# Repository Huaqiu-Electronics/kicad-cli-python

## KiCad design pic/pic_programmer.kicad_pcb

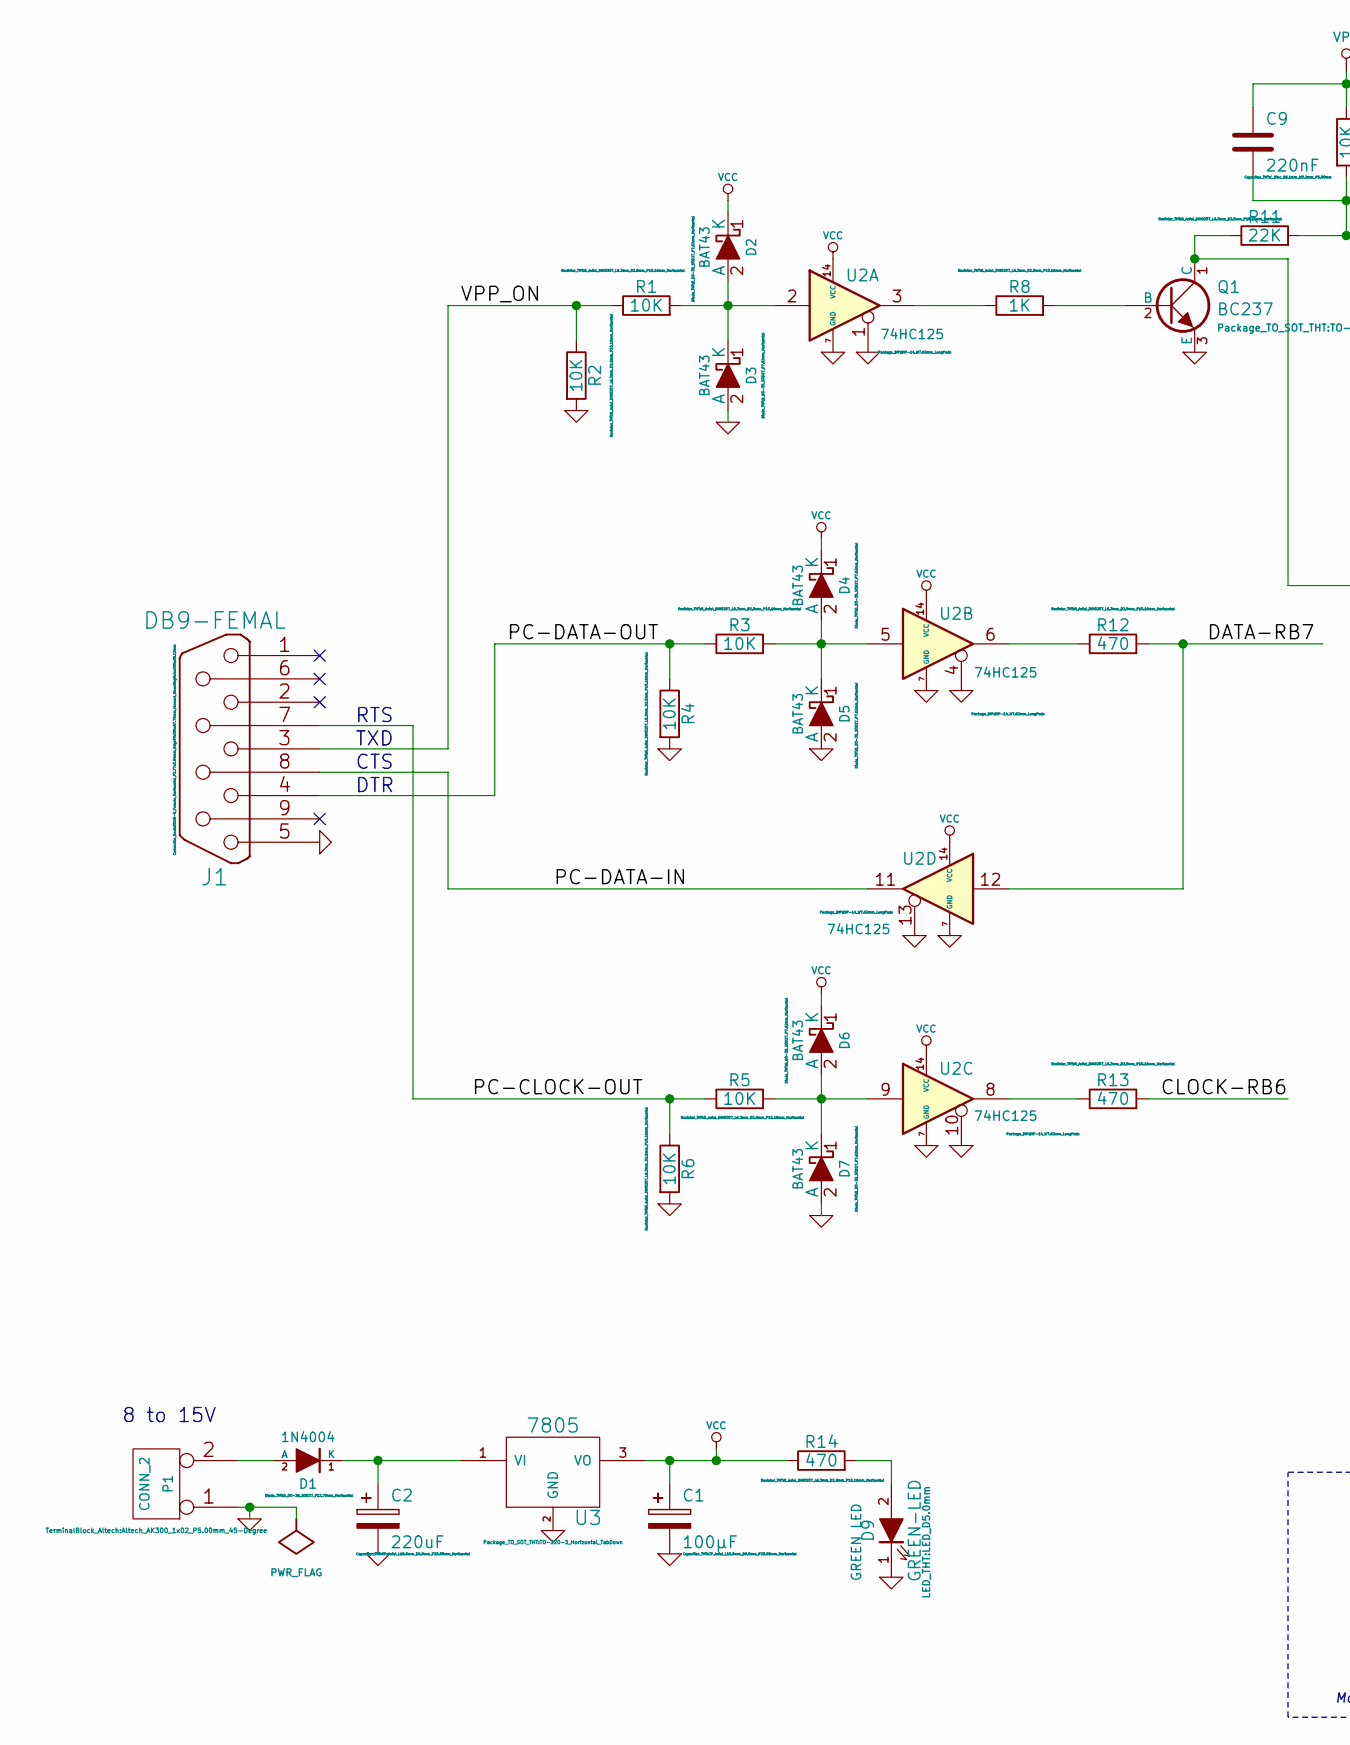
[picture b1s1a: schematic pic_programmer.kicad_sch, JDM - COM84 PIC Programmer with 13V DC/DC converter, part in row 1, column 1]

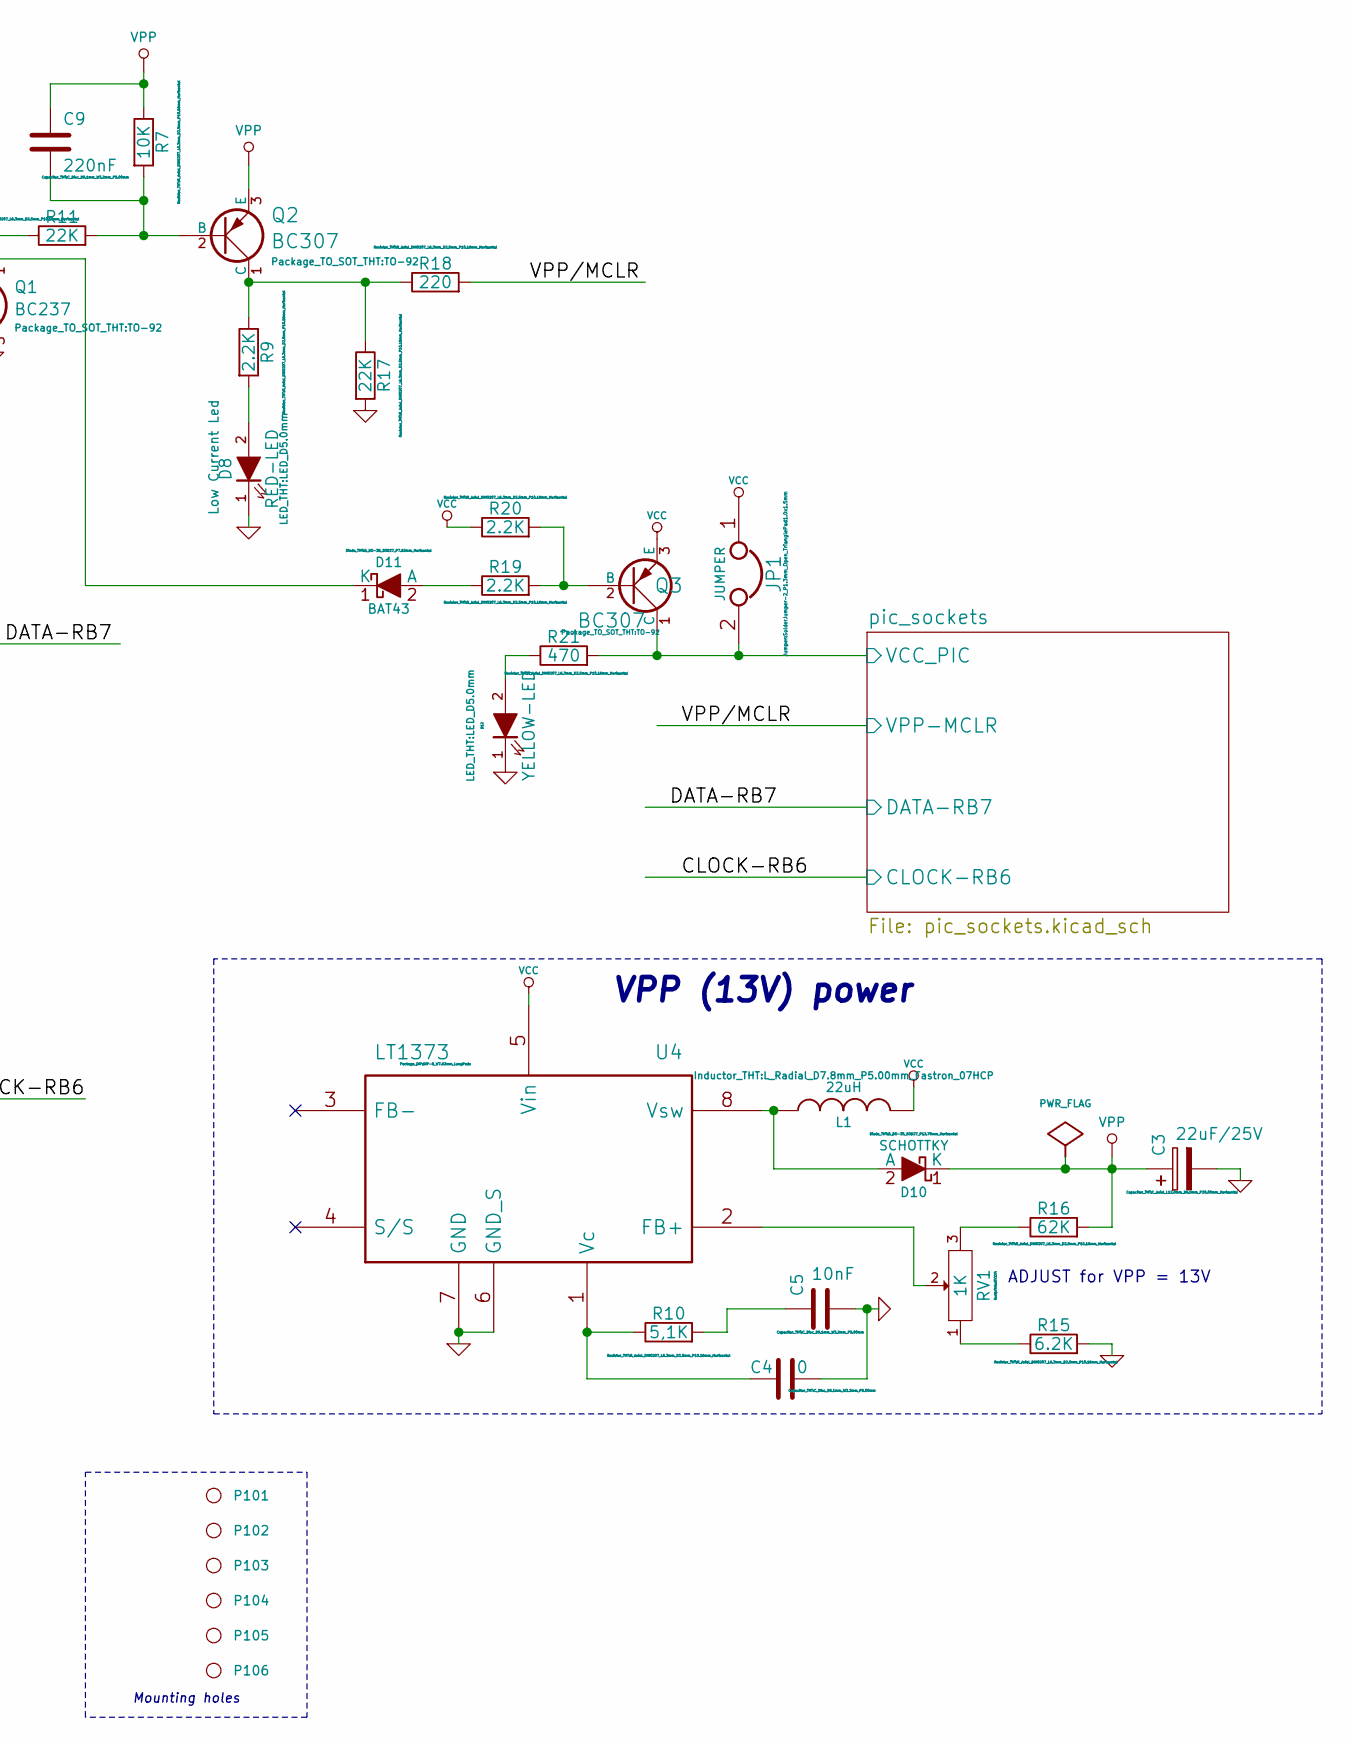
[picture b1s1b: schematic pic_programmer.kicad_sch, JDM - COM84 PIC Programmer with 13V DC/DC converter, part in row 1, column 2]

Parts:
C1: 100µF; CP_Axial_L18.0mm_D6.5mm_P25.00mm_Horizontal
C2: 220uF; CP_Axial_L18.0mm_D6.5mm_P25.00mm_Horizontal
C3: 22uF/25V; C_Axial_L12.0mm_D6.5mm_P20.00mm_Horizontal
C4: 0; C_Disc_D5.1mm_W3.2mm_P5.00mm
C5: 10nF; C_Disc_D5.1mm_W3.2mm_P5.00mm
C9: 220nF; C_Disc_D5.1mm_W3.2mm_P5.00mm
D1: 1N4004; D_DO-35_SOD27_P12.70mm_Horizontal
D2, D3, D4, D5, D6, D7, D11: BAT43; D_DO-35_SOD27_P7.62mm_Horizontal
D8: RED-LED; LED_D5.0mm
D9: GREEN-LED; LED_D5.0mm
D10: SCHOTTKY; D_DO-35_SOD27_P12.70mm_Horizontal
D12: YELLOW-LED; LED_D5.0mm
J1: DB9-FEMAL; DSUB-9_Female_Horizontal_P2.77x2.84mm_EdgePinOffset7.70mm_H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
JP1: JUMPER; SolderJumper-2_P1.3mm_Open_TrianglePad1.0x1.5mm
L1: 22uH; L_Radial_D7.8mm_P5.00mm_Fastron_07HCP
P1: CONN_2; Altech_AK300_1x02_P5.00mm_45-Degree
P101, P102, P103, P104, P105, P106: CONN_1; MountingHole_4.3mm_M4
Q1: BC237; TO-92
Q2, Q3: BC307; TO-92
R1, R2, R3, R4, R5, R6, R7: 10K; R_Axial_DIN0207_L6.3mm_D2.5mm_P10.16mm_Horizontal
R8: 1K; R_Axial_DIN0207_L6.3mm_D2.5mm_P10.16mm_Horizontal
R9, R19, R20: 2.2K; R_Axial_DIN0207_L6.3mm_D2.5mm_P10.16mm_Horizontal
R10: 5,1K; R_Axial_DIN0207_L6.3mm_D2.5mm_P10.16mm_Horizontal
R11, R17: 22K; R_Axial_DIN0207_L6.3mm_D2.5mm_P10.16mm_Horizontal
R12, R13, R14, R21: 470; R_Axial_DIN0207_L6.3mm_D2.5mm_P10.16mm_Horizontal
R15: 6.2K; R_Axial_DIN0207_L6.3mm_D2.5mm_P10.16mm_Horizontal
R16: 62K; R_Axial_DIN0207_L6.3mm_D2.5mm_P10.16mm_Horizontal
R18: 220; R_Axial_DIN0207_L6.3mm_D2.5mm_P10.16mm_Horizontal
RV1: 1K; RV2X4
U2: 74HC125; DIP-14_W7.62mm_LongPads
U3: 7805; TO-220-3_Horizontal_TabDown
U4: LT1373; DIP-8_W7.62mm_LongPads

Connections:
/CLOCK-RB6: R13.2; also elsewhere on the board
/DATA-RB7: R12.2, U2.12; also elsewhere on the board
/PC-CLOCK-OUT: J1.7, R5.1, R6.1
/PC-DATA-IN: J1.8, U2.11
/PC-DATA-OUT: J1.4, R3.1, R4.1
/VPP_ON: J1.3, R1.1, R2.1
/VPP/MCLR: R18.2; also elsewhere on the board
/pic_sockets/VCC_PIC: JP1.2, Q3.1 (C), R21.2; also elsewhere on the board
GND: C1.2, C2.2, C3.2, C4.2, C5.2, D3.2 (A), D5.2 (A), D7.2 (A), D8.1 (K), D9.1 (K), D12.1 (K), J1.5, P1.1, Q1.3 (E), R2.2, R4.2, R6.2, R15.2, R17.2, U2.1, U2.4, U2.7 (GND), U2.10, U2.13, U3.2 (GND), U4.6 (GND_S), U4.7 (GND); also elsewhere on the board
unnamed: C5.1, R10.2
unnamed: D1.2 (A), P1.2 (PM)
unnamed: C2.1, D1.1 (K), U3.1 (VI)
unnamed: D2.2 (A), D3.1 (K), R1.2, U2.2
unnamed: D4.2 (A), D5.1 (K), R3.2, U2.5
unnamed: D6.2 (A), D7.1 (K), R5.2, U2.9
unnamed: D8.2 (A), R9.2
unnamed: D9.2 (A), R14.2
unnamed: D10.2 (A), L1.1, U4.8 (Vsw)
unnamed: D11.2 (A), R19.1
unnamed: D11.1 (K), Q1.1 (C), R11.1
unnamed: D12.2 (A), R21.1
unnamed: Q1.2 (B), R8.2
unnamed: C9.2, Q2.2 (B), R7.2, R11.2
unnamed: Q2.1 (C), R9.1, R17.1, R18.1
unnamed: Q3.2 (B), R19.2, R20.2
unnamed: R8.1, U2.3
unnamed: R12.1, U2.6
unnamed: R13.1, U2.8
unnamed: R15.1, RV1.1
unnamed: R16.1, RV1.3
unnamed: RV1.2, U4.2 (FB+)
unnamed: C4.1, R10.1, U4.1 (Vc)
VCC: C1.1, D2.1 (K), D4.1 (K), D6.1 (K), JP1.1, L1.2, Q3.3 (E), R14.1, R20.1, U2.14 (VCC), U3.3 (VO), U4.5 (Vin)
VPP: C3.1, C9.1, D10.1 (K), Q2.3 (E), R7.1, R16.2

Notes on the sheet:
ADJUST for VPP = 13V
8 to 15V
VPP (13V) power
RTS
TXD
CTS
DTR
Mounting holes

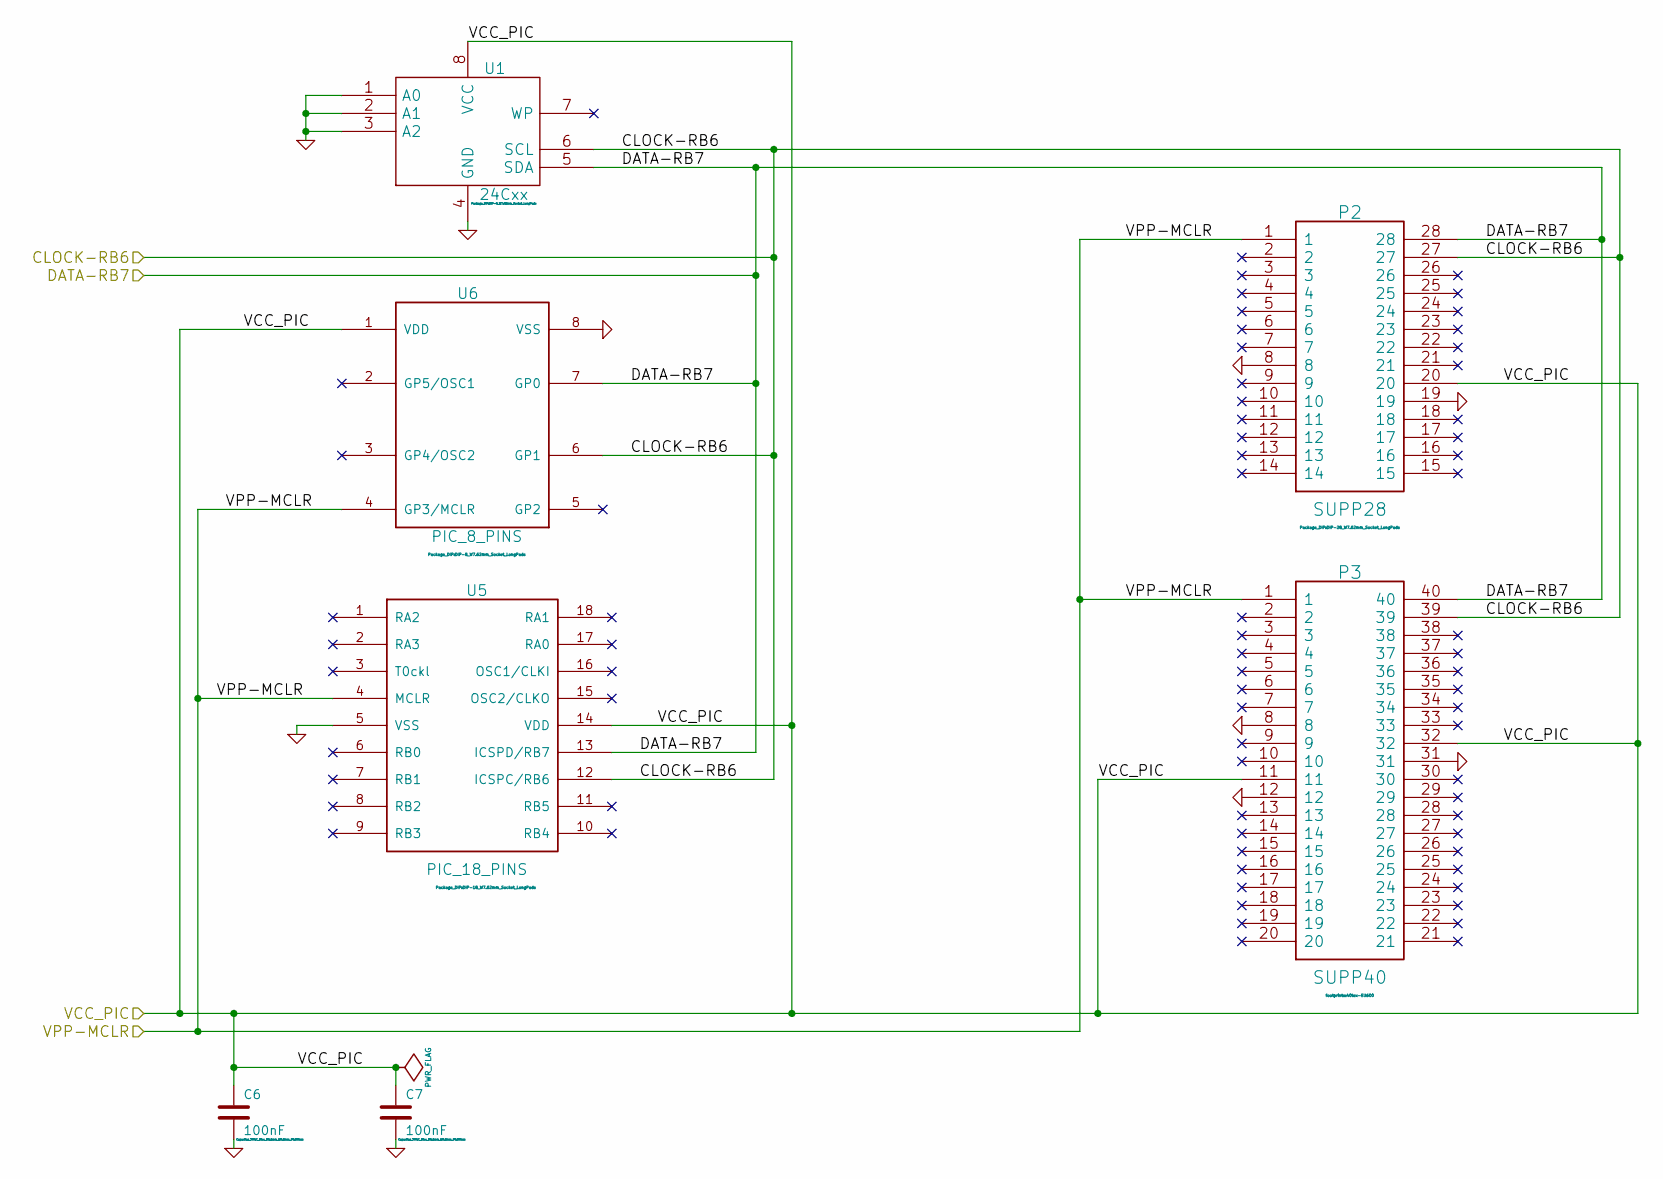
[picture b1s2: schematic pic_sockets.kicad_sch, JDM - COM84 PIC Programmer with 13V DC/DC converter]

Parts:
C6, C7: 100nF; C_Disc_D5.1mm_W3.2mm_P5.00mm
P2: SUPP28; DIP-28_W7.62mm_Socket_LongPads
P3: SUPP40; 40tex-Ell600
U1: 24Cxx; DIP-8_W7.62mm_Socket_LongPads
U5: PIC_18_PINS; DIP-18_W7.62mm_Socket_LongPads
U6: PIC_8_PINS; DIP-8_W7.62mm_Socket_LongPads

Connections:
/CLOCK-RB6: P2.27, P3.39, U1.6 (SCL), U5.12 (ICSPC/RB6), U6.6 (GP1); also elsewhere on the board
/DATA-RB7: P2.28, P3.40, U1.5 (SDA), U5.13 (ICSPD/RB7), U6.7 (GP0); also elsewhere on the board
/VPP/MCLR: P2.1, P3.1, U5.4 (MCLR), U6.4 (GP3/MCLR); also elsewhere on the board
/pic_sockets/VCC_PIC: C6.1, C7.1, P2.20, P3.11, P3.32, U1.8 (VCC), U5.14 (VDD), U6.1 (VDD); also elsewhere on the board
GND: C6.2, C7.2, P2.8, P2.19, P3.8, P3.12, P3.31, U1.1 (A0), U1.2 (A1), U1.3 (A2), U1.4 (GND), U5.5 (VSS), U6.8 (VSS); also elsewhere on the board

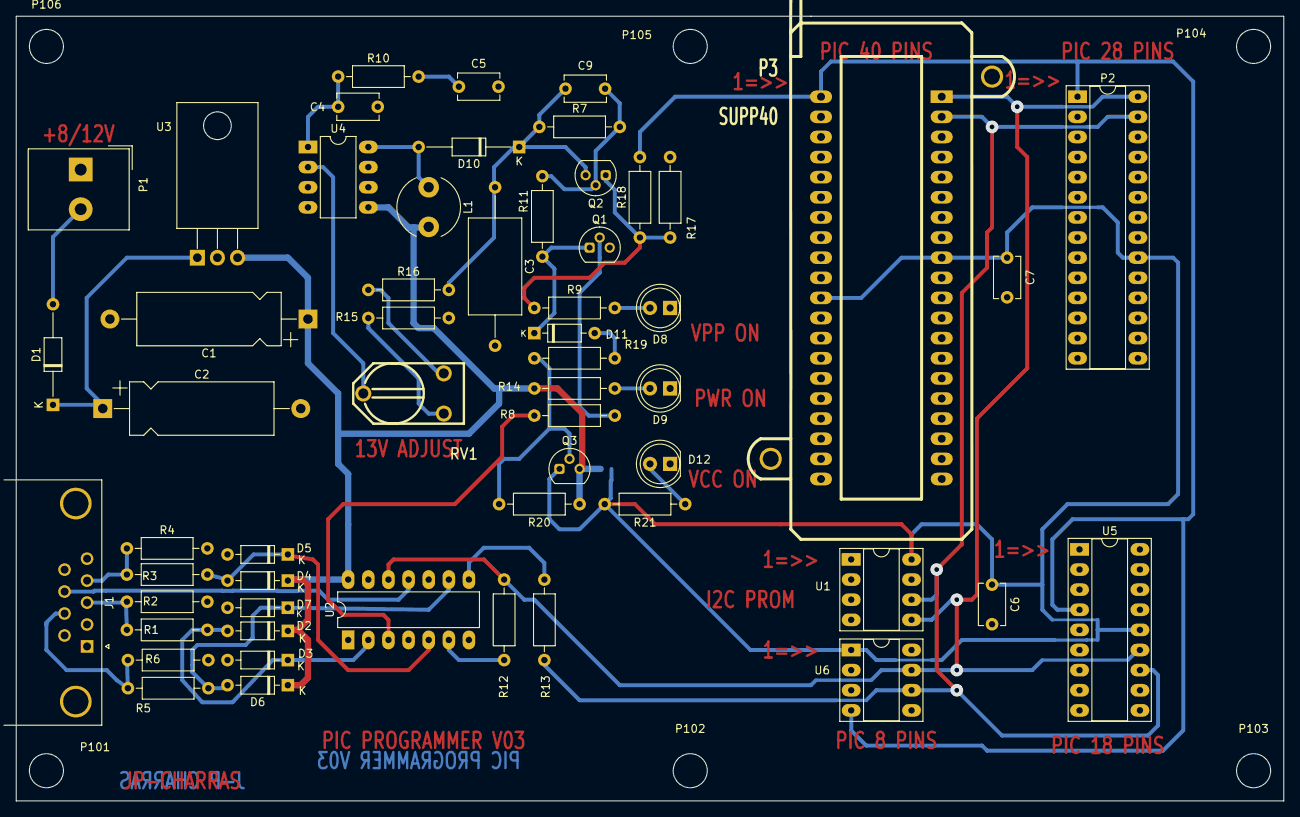
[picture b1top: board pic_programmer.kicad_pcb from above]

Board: 2 copper layers, 160.0 x 99.1 mm, 63 parts (1 on the bottom side), 34 nets.

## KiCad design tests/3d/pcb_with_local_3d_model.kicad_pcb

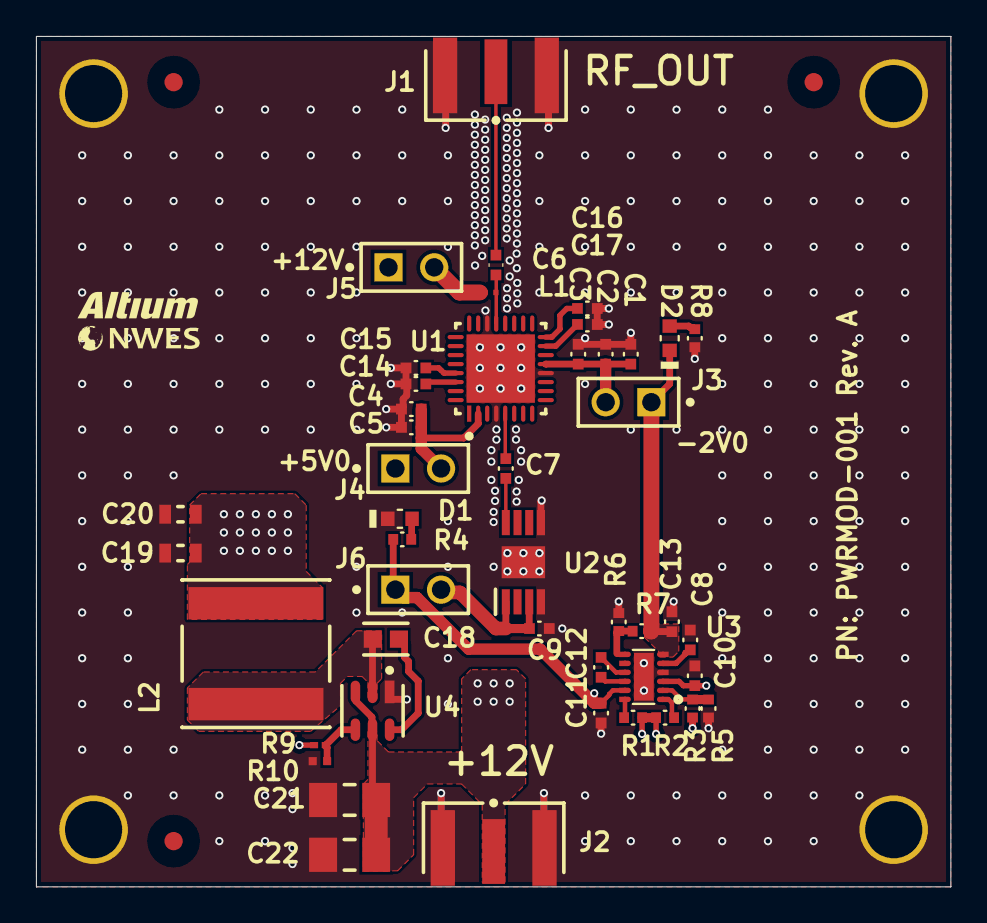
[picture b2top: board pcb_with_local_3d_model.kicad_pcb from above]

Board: 4 copper layers, 50.8 x 47.2 mm, 46 parts (0 on the bottom side), 29 nets.

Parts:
C1, C8, C12, C15, C16: 4.7uF; 0402_CAP
C2, C4, C5, C6, C7, C14, C17: 1000pF; 0402_CAP
C3: 100pF; 0402_CAP
C9: 10uF; 0402_CAP
C10, C11, C13: 2.2uF; 0402_CAP
C18: C0603C104Z3VACTU; FP-C0603-CG-IPC_B
C19, C20: C1608X5R1A226M080AC; CAPC1608X100X20ML10
C21, C22: GRM31CR61E106KA12L; CAPC3216X180X55ML20T25
D1, D2: GRN; LED_0603
J1, J2: SMA-J-P-H-ST-EM1; FP-SMA-J-P-H-ST-EM1-MFG
J3, J4, J5, J6: M20-9990246; FP-M20-9990246-MFG
L1: 1.2nH; IND_0201
L2: NRS8030T3R3MJGJ; FP-NRS8030-MFG
R1, R2, R5, R6: 10K; 0402_RES
R3: 15K; 0402_RES
R4, R8: 120; 0402_RES
R7: 6.34K; 0402_RES
R9: CRCW020156K2FNED; RESC0603X28X15NL05T05
R10: ERJ2RKF1002X; RESC1005X40X25LL05T05
U1: HMC637ALP5E; FP-HCP-32-1-IPC_A
U2: HMC358MS8GE; SOP65P488X110-9N
U3: LM27762DSSR; SON50P200X300X80-13N-D
U4: TPS562201DDCR; FP-DDC0006A-IPC_C

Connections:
3V0: C11.2, J6.1, R3.1, R4.1, U3.11
5V0: C10.2, C19.2, C20.2, J4.1, L2.2, R1.1, R2.1, R9.2, U3.3
+12V: C21.2, C22.2, J2.1, J5.1, U4.3, U4.5
-2V0: C13.1, D2.2, J3.1, R7.2, U3.6
GND: C1.1, C2.1, C3.1, C4.1, C5.1, C8.2, C9.1, C10.1, C11.1, C13.2, C14.1, C15.1, C16.1, C17.1, C19.1, C20.1, C21.1, C22.1, D1.2, J1.2, J1.3, J1.4, J1.5, J2.2, J2.3, J2.4, J2.5, R5.2, R6.1, R8.1, R10.1, U1.4, U1.12, U1.22, U1.33, U2.4, U2.5, U2.9, U3.4, U3.13, U4.1
LO OUT: C6.1, J1.1
NetC6_2: C6.2, L1.2, U1.21
NetC7_1: C7.1, U2.8
NetC7_2: C7.2, U1.5
NetC8_1: C8.1, U3.5
NetC12_1: C12.1, U3.9
NetC12_2: C12.2, U3.10
NetC14_2: C14.2, U1.30
NetC15_2: C15.2, U1.29
NetC16_2: C16.2, U1.16
NetC17_2: C17.2, U1.15
NetC18_2: C18.2, U4.6
NetD1_1: D1.1, R4.2
NetD2_1: D2.1, R8.2
NetR1_2: R1.2, U3.12
NetR2_2: R2.2, U3.1
NetR3_2: R3.2, R5.1, U3.2
NetR6_2: R6.2, R7.1, U3.7
NetR9_1: R9.1, R10.2, U4.4
SW_OUT: C18.1, L2.1, U4.2
VCC: C9.2, J6.2, U2.1, U2.3
VDD: J5.2, L1.1
VGG1: C1.2, C2.2, C3.2, J3.2, U1.13
VGG2: C4.2, C5.2, J4.2, U1.2

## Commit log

2024-06-21 update local test
2024-06-21 fix get local ip
2024-07-23 Update KICAD_FULL_IMAGE_ID
2024-08-21 Fix the convert script
2024-08-21 Add batch_convert_pcb_to_glb
2024-09-10 Update kicad cli cmd
2024-09-10 Update ci cmd
2024-09-10 update demo
2024-09-11 Do not export the zones
2024-09-11 Add compress cmd
2024-09-11 export zones and soldermask
2024-09-11 Pretty the cmd args
2025-03-13 Add 9.0 fs
2025-03-13 Add BUG PIC
2025-07-29 refactor(export_net_list): update script to export net list for pic_sockets
    - Comment out previous test file path
    - Add new test file path for pic_sockets
    - Call export_net_list_local and export_net_list functions with the new file path
2025-09-03 build(ad): add Altium design files for PWRMOD-001-RevA
    - Add PWRMOD-001-RevA.PcbDoc and PWRMOD-001-RevA.SchDoc files
    - Update convert_altium.py to reference the new PCB file
2025-09-03 fix: types/v3-directive not published
2025-09-03 chore: update .gitignore file
    - Remove unnecessary ignored file types and folders
    - Add 'tests/out' folder to be ignored
    - Keep '*.glb' files ignored
2025-09-03 test(kicad-cli): add integration tests for kicad-cli
    - Add PowerShell and Python scripts for testing kicad-cli functionality
    - Implement tests for PCB and schematic conversion
    - Add test for 3D model (GLB) export
    - Update .gitignore to exclude test output files
2025-09-19 feat: add start_kicad_server.py script
    - Create new script to start KiCad server using Docker
    - Implement function to run KiCad CLI server inside a container
    - Add main function to test server startup with example path
2025-09-23 ``` feat(export): add binary export files for video project
    Added the following binary export files:
    - video.glb.zip
    - video.kicad_pcb.zip
    - video.kicad_sch.zip
    These files contain the exported assets for the video project including
    3D models and KiCad design files.
